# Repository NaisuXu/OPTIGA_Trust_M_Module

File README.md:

# OPTIGA_Trust_M_Module

## Brief

[Infineon OPTIGA Trust M](https://www.infineon.com/cms/cn/product/security-smart-card-solutions/optiga-embedded-security-solutions/optiga-trust/optiga-trust-m-sls32aia/) IC Board. 

This project is designed with [Kicad](https://www.kicad.org/).

## License
<br />This work is licensed under a <a rel="license" href="http://creativecommons.org/licenses/by-sa/4.0/">Creative Commons Attribution-ShareAlike 4.0 International License</a>.

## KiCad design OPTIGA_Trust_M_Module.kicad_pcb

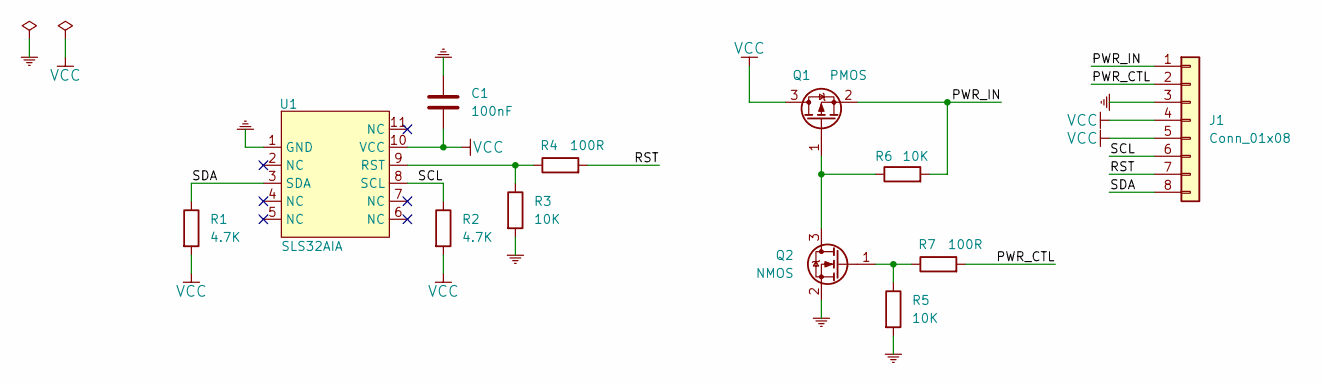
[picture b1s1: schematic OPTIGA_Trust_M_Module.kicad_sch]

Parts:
C1: 100nF; C_0603_1608Metric_Pad1.08x0.95mm_HandSolder
J1: Conn_01x08; PinSocket_1x08_P2.54mm_Vertical
Q1: PMOS; SOT-23
Q2: NMOS; SOT-23
R1, R2: 4.7K; R_0603_1608Metric_Pad0.98x0.95mm_HandSolder
R3, R5, R6: 10K; R_0603_1608Metric_Pad0.98x0.95mm_HandSolder
R4, R7: 100R; R_0603_1608Metric_Pad0.98x0.95mm_HandSolder
U1: SLS32AIA; USON-10-1EP_3x3mm_P0.5mm_EP1.5x2.3mm

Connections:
/PWR_CTL: J1.2, R7.2
/PWR_IN: J1.1, Q1.2 (S), R6.2
/RST: J1.7, R4.2
/SCL: J1.6, R2.1, U1.8 (SCL)
/SDA: J1.8, R1.1, U1.3 (SDA)
GND: C1.1, J1.3, Q2.2 (S), R3.2, R5.2, U1.1 (GND)
unnamed: Q1.1 (G), Q2.3 (D), R6.1
unnamed: Q2.1 (G), R5.1, R7.1
unnamed: R3.1, R4.1, U1.9 (RST)
VCC: C1.2, J1.4, J1.5, Q1.3 (D), R1.2, R2.2, U1.10 (VCC)

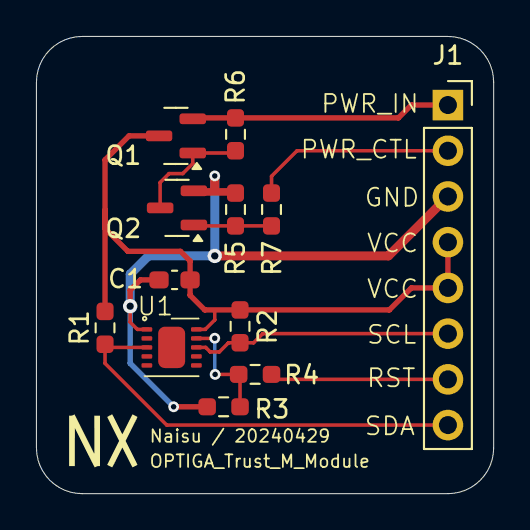
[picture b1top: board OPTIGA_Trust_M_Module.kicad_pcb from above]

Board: 2 copper layers, 25.4 x 25.4 mm, 12 parts (0 on the bottom side), 10 nets.

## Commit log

2024-04-24 add: README.md
2024-04-29 modify: i2c pull-up resistor value
2024-04-29 modify: uson-10 footprint
